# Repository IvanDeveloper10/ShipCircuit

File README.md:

# 🚢 Ship Circuit

**ShipCircuit** is a circuit that has two functions, the first is to control an LED with a potentiometer, while the second is to turn on the LEDs only when the button is pressed.

I built the welding project for Hack Club. (https://github.com/hackclub/solder)!

---

## ✨ What It Does

The circuit has one LED controlled by a potentiometer while the other 3 LEDs are controlled by a push button.

---

## 📦 Bill of Materials

| Component         | Quantity | Notes                             |
|------------------|----------|-----------------------------------|
| Potentiometer                 | 1 | Vary current                    |
| Battery Cell                  | 1 | Power                           |
| 220Ω Resistor                 | 3 | Reduce current                  |
| 10µF Electrolytic Capacitor   | 1 | Debounces fast flickers         |
| 5mm LED                       | 4 | Light output                    |
| PCB / Breadboard              | 1 | Custom-designed PCB             |
| Switch Push                   | 1 | current step                    |

---

## 📐 Circuit Design

### 🧠 Schematic

### 🧩 PCB Layout

### 🔭 3D View 1

### 🔬 3D View 2

### 3D View Back

> All files live in the `kicad/` and `gerbers/` folders.

---

## 🛠️ Files in This Repo

```

ShipCircuit/
├── kicad/         → KiCad project
├── gerbers/       → Gerber + drill files (for fabrication)
├── images/          → Screenshots: schematic, PCB, 3D views
└── README.md      → You’re here!

```

---

## 🧪 Testing It

Power the circuit using a coin cell.  
Then:
- ✅ Increase or decrease the signal from the potentiometer to the LED.
- ✅ Press the button to turn on all 3 LEDs.

---

## 🙋 Slack Username

Ivan P

SLACK ID: T0266FRGM

---

## 🚀 Why I Made This

Because I had never tried kiCad before and I thought it would be a wonderful idea to be able to learn and create something while being in an environment surrounded by hackers.

---

Built for [Hack Club Solder](https://github.com/hackclub/solder) 💚

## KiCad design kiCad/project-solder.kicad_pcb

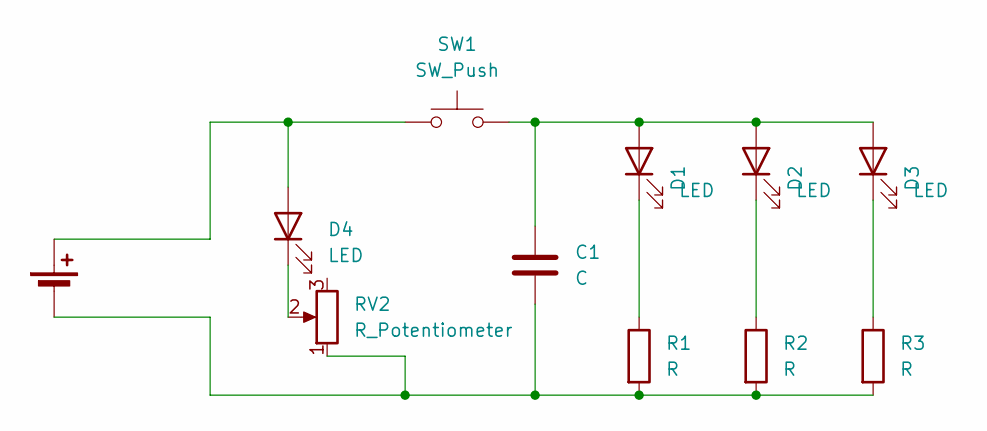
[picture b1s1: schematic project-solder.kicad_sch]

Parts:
BT1: Battery_Cell; BatteryHolder_Keystone_3034_1x20mm
C1: C; CP_Radial_D8.0mm_P5.00mm
D1, D2, D3, D4: LED; LED_D5.0mm
R1, R2, R3: R; R_Axial_DIN0207_L6.3mm_D2.5mm_P7.62mm_Horizontal
RV2: R_Potentiometer; Potentiometer_Vishay_T73YP_Vertical
SW1: SW_Push; SW_PUSH_6mm

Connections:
unnamed: BT1.1 (+), D4.2 (A), SW1.1
unnamed: BT1.2 (-), C1.2, R1.2, R2.2, R3.2, RV2.1
unnamed: C1.1, D1.2 (A), D2.2 (A), D3.2 (A), SW1.2
unnamed: D1.1 (K), R1.1
unnamed: D2.1 (K), R2.1
unnamed: D3.1 (K), R3.1
unnamed: D4.1 (K), RV2.2

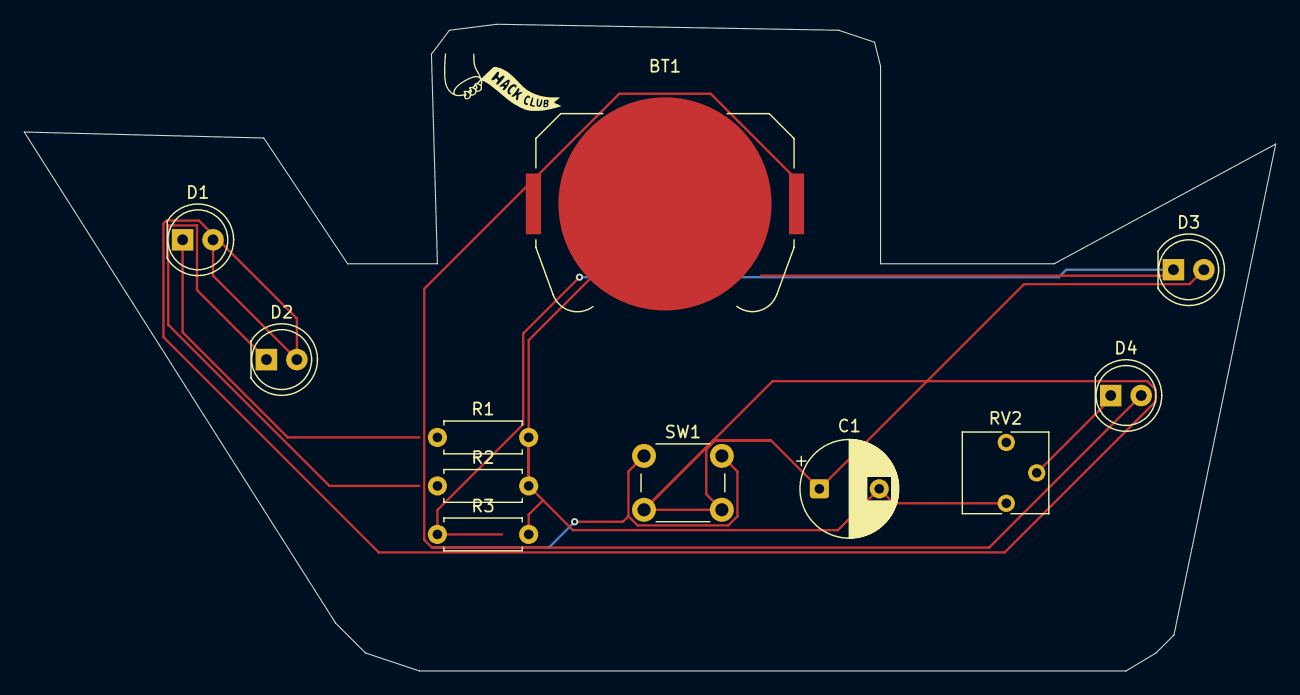
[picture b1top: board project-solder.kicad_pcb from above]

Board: 2 copper layers, 104.5 x 54.0 mm, 12 parts (0 on the bottom side), 7 nets.

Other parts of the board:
  : LOGO

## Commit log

2025-06-30 Create main
